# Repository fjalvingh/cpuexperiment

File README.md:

# Experiments with a am29xx based CPU

The am29xx series of bitslice CPU parts were a big thing when they arrived, and they have been used in many vintage designs. I find them interesting because they are still reasonably simple to understand, and they do replace a large amount of TTL logic for a homebrew CPU. I got a few of these parts from different places and decided to play with them to get an idea on how they work.

To do that the plan is to build some parts for a real CPU. It is not intended to be finished, it is intended to teach me and help me understand these parts, and to help me understand what is important in a CPU design using them.

## Process

NONE OF THIS IS READY FOR ANYTHING!! DO NOT ORDER BOARDS, they will not work ;)

### The ALU, getting to know the am2901

I am starting with the ALU part as I got 4 am2901's in my parts bin ;) I want to make a 16 bit ALU out of them, and the 2901's would also contain the generic register set (r0..r15).
I did consider breadboarding that, but 16 bits is a lot of wires, reliable breadboards are pretty expensive, and I really, *really* did not feel like wiring that all up...
So instead I created a Kicad schematic hoping that I would not be too far off, and I created a PCB using the Autorouter to route most traces so that I would not waste time on that. It is a 2 layer board so making fixes for the mistakes I've undoubtedly made should not be too difficult.

The board has 4x am2901, some glue logic to detect condition codes, a lot of leds to show ALU function inputs, and two sockets for my [8 bit bus to hex display](https://github.com/fjalvingh/8bit-busdisplay) so that we can easily follow what is happening.

The board uses two 40 pin double row pin headers (female) as a connector to a later possible backplane, as these are cheap and relatively reliable. And they make it easy to exercise the board using an Arduino Mega 2560.

A picture of the completed board:

The wires into the connectors are breadboard patch wires, and they prove to be useless, so the next try is to make real pin header wires to the Arduino.

### Playing with the board

After creating proper cabling between the Arduino and the ALU board:

at least everything worked consistently. But writing Arduino programs makes it a bit hard to do a lot of testing. So the next part is to make the Arduino a slave board that gets commands over USB Serial from a Java program. The Java program sends simple packets consisting of a command code, parameter values and a checksum. The Arduino waits for commands on its bus, decodes the packets, then executes the command. After that it sends either an error packet or a response packet back with any results for the command.

These are the programs under aluboard-controller and aluboard-arduino.

## Progress

* 2025/11/28 Added basic Java GUI and an Arduino program to test the ALU board
* 2025/11/23 Created this Github repo
* 2025/10/18 Started the ALU Kicad design

## Documentation used

I am using the following documents to make sense of everything.

### AM29xx series:
 
* [The AM2900 family data book](documentation/1978_The_Am2900_Family_Data_Book.pdf)
* [The am2901 datasheet](documentation/AM2901-AdvancedMicroDevices.pdf)
* [The am2910 datasheet](documentation/am2910.pdf)
* [Bit Slice microprocessor design](http://www.bitsavers.org/components/amd/bitslice/Mick_Bit-Slice_Microprocessor_Design_1980.pdf) by John Mick and Jim Brick
* [am2910 application note: programming the 2910](documentation/Am2910_apnote_Programming%20the.pdf)
* A more readable [am2901 block diagram](documentation/am2901-blockdiagram.jpg)
* Bit slice design - controllers and ALUs by [Donnamaie White](https://www.donnamaie.com/) - whose site has a lot of other interesting information.
* The "Build a microcomputer" series of appnotes, also [on the site of Donnamaie White, here](https://www.donnamaie.com/AMD_2900.html).
* [A microprogrammed computer](documentation/16-bit%20computer%20book.pdf), also from Donnamaie's site.

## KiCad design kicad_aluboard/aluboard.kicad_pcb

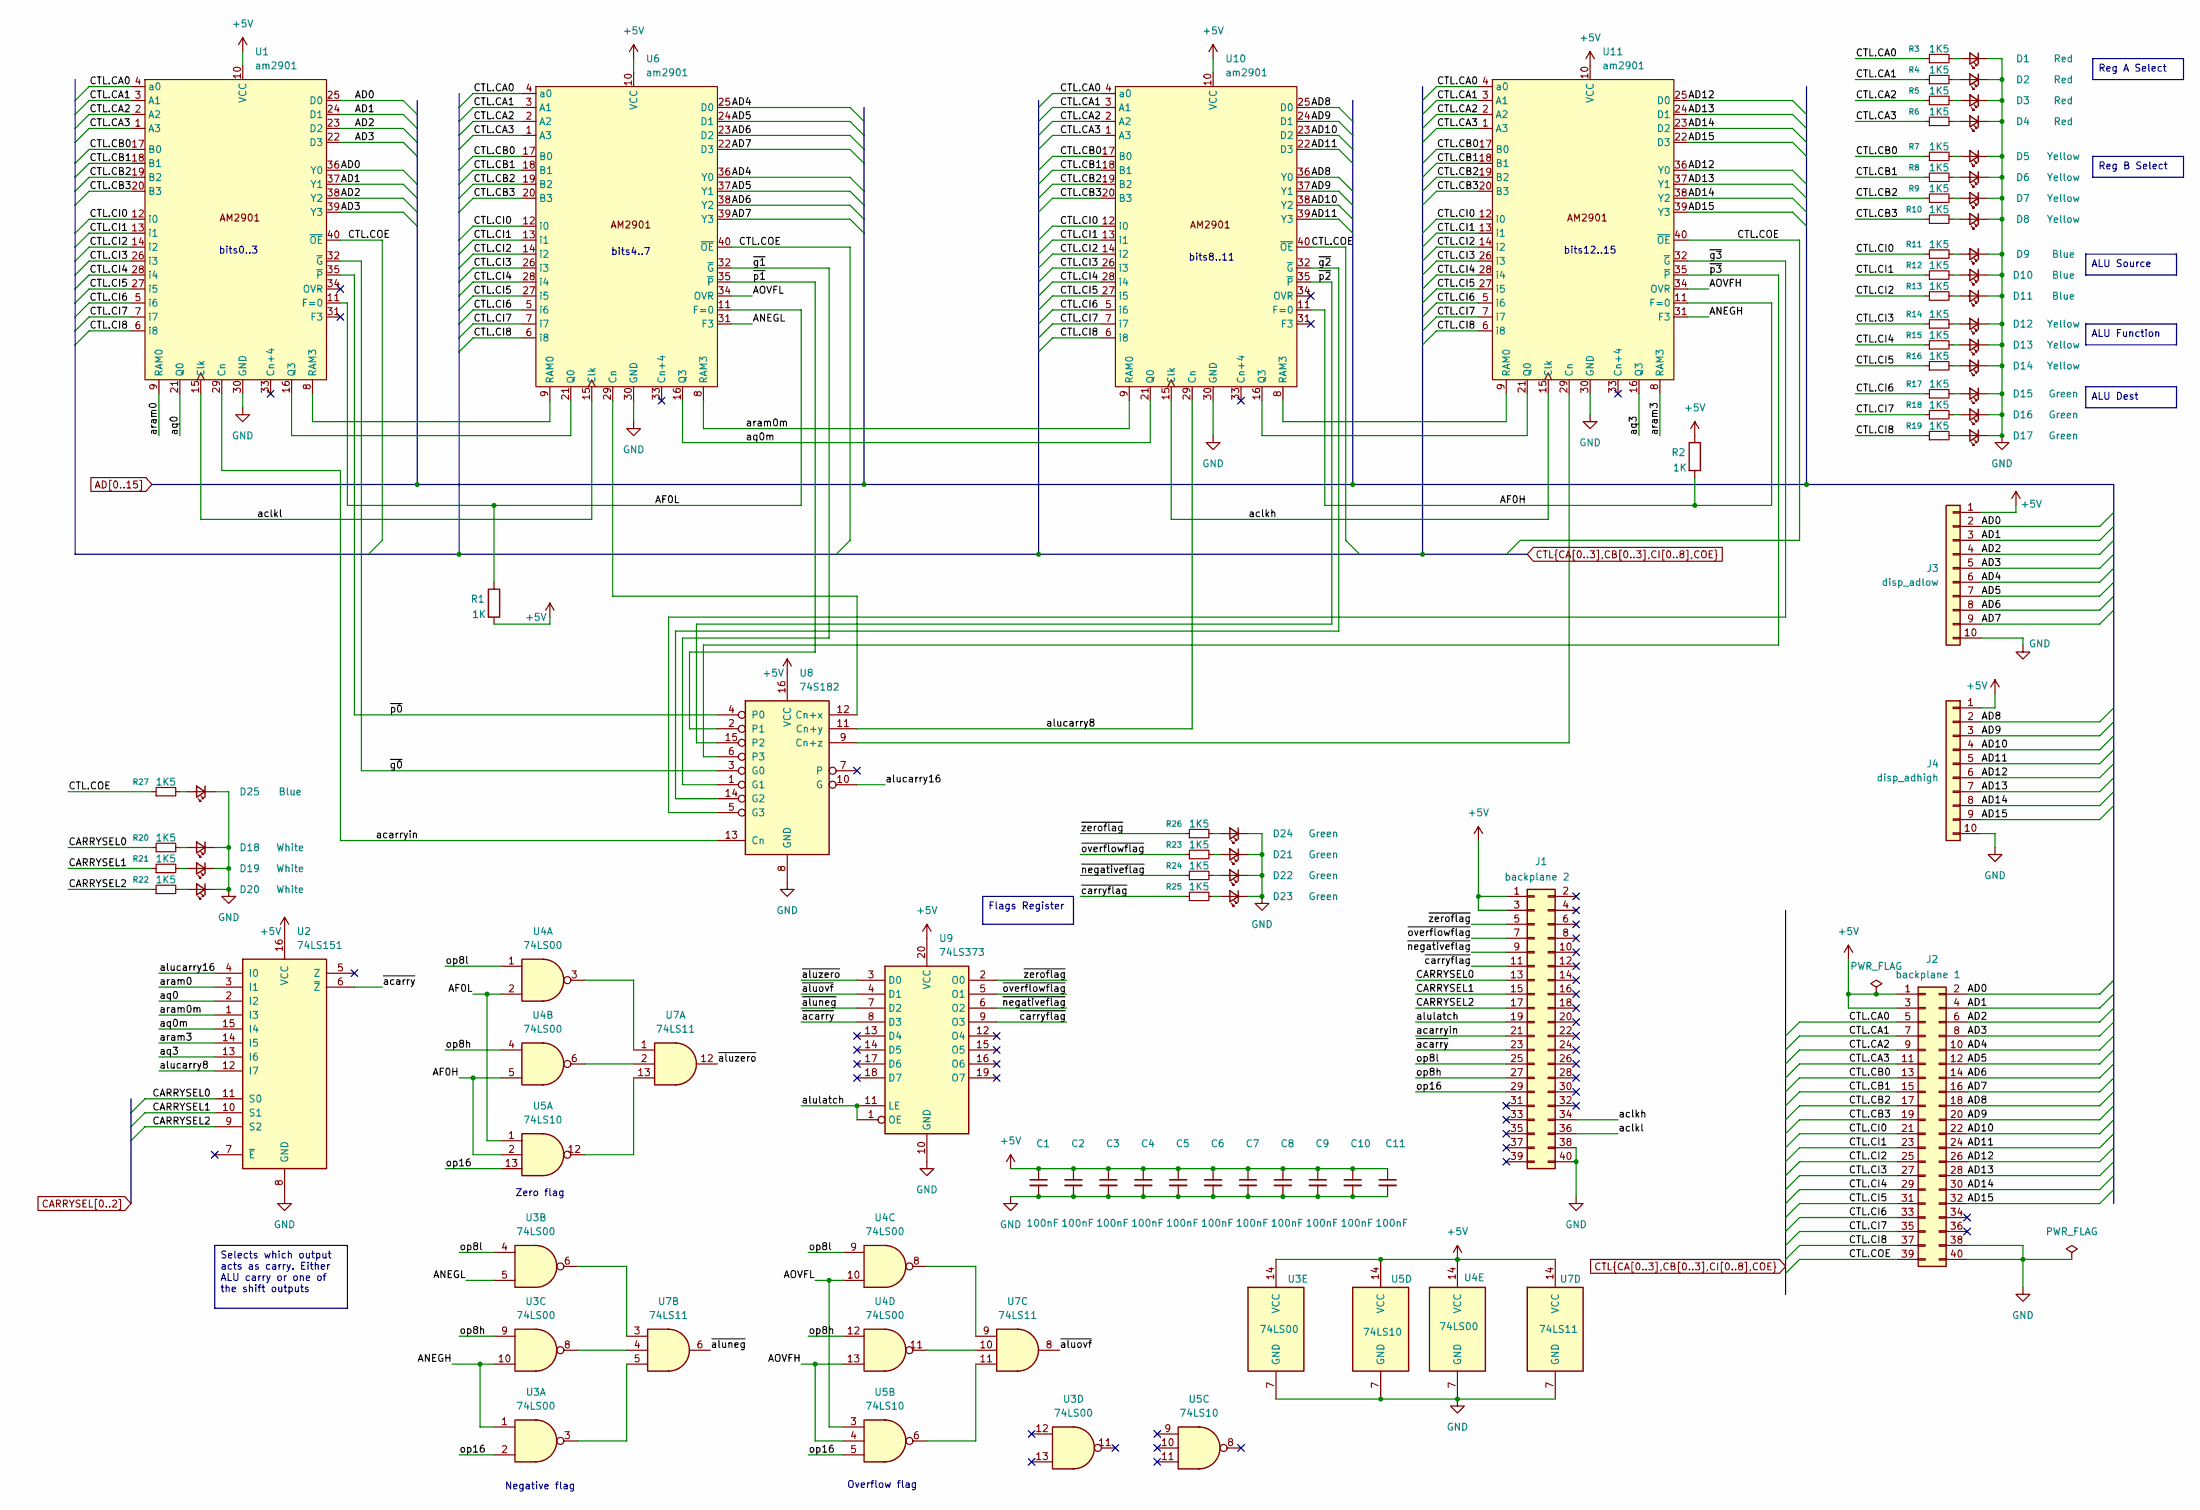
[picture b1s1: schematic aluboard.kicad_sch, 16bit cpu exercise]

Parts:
C1, C2, C3, C4, C5, C6, C7, C8, C9, C10, C11: 100nF; C_Disc_D3.8mm_W2.6mm_P2.50mm
D1, D2, D3, D4: Red; LED_0805_2012Metric_Pad1.15x1.40mm_HandSolder
D5, D6, D7, D8, D12, D13, D14: Yellow; LED_0805_2012Metric_Pad1.15x1.40mm_HandSolder
D9, D10, D11, D25: Blue; LED_0805_2012Metric_Pad1.15x1.40mm_HandSolder
D15, D16, D17, D21, D22, D23, D24: Green; LED_0805_2012Metric_Pad1.15x1.40mm_HandSolder
D18, D19, D20: White; LED_0805_2012Metric_Pad1.15x1.40mm_HandSolder
J1: backplane 2; PinSocket_2x20_P2.54mm_Horizontal
J2: backplane 1; PinSocket_2x20_P2.54mm_Horizontal
J3: disp_adlow; PinSocket_1x10_P2.54mm_Vertical
J4: disp_adhigh; PinSocket_1x10_P2.54mm_Vertical
R1, R2: 1K; R_Axial_DIN0207_L6.3mm_D2.5mm_P7.62mm_Horizontal
R3, R4, R5, R6, R7, R8, R9, R10, R11, R12, R13, R14, R15, R16, R17, R18, R19, R20, R21, R22, R23, R24, R25, R26, R27: 1K5; R_0805_2012Metric
U1, U6, U10, U11: am2901; DIP-40_W15.24mm_Socket_LongPads
U2: 74LS151; DIP-16_W7.62mm_Socket_LongPads
U3, U4: 74LS00; DIP-14_W7.62mm_Socket_LongPads
U5: 74LS10; DIP-14_W7.62mm_Socket_LongPads
U7: 74LS11; DIP-14_W7.62mm_Socket_LongPads
U8: 74S182; DIP-16_W7.62mm_Socket_LongPads
U9: 74LS373; DIP-20_W7.62mm_Socket_LongPads

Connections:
+5V: C1.1, C2.1, C3.1, C4.1, C5.1, C6.1, C7.1, C8.1, C9.1, C10.1, C11.1, J1.1, J1.3, J2.1, J2.3, J3.1, J4.1, R1.2, R2.1, U1.10 (VCC), U2.16 (VCC), U3.14 (VCC), U4.14 (VCC), U5.14 (VCC), U6.10 (VCC), U7.14 (VCC), U8.16 (VCC), U9.20 (VCC), U10.10 (VCC), U11.10 (VCC)
/AF0H: R2.2, U4.5, U5.2, U10.11 (F=0), U11.11 (F=0)
/AF0L: R1.1, U1.11 (F=0), U4.2, U5.1, U6.11 (F=0)
/ANEGH: U3.1, U3.10, U11.31 (F3)
/ANEGL: U3.5, U6.31 (F3)
/AOVFH: U4.13, U5.4, U11.34 (OVR)
/AOVFL: U4.10, U5.3, U6.34 (OVR)
/acarryin: J1.21, U1.29 (Cn), U8.13 (Cn)
/aclkh: J1.34, U10.15 (Clk), U11.15 (Clk)
/aclkl: J1.36, U1.15 (Clk), U6.15 (Clk)
/alucarry8: U2.12 (I7), U8.11 (Cn+y), U10.29 (Cn)
/alucarry16: U2.4 (I0), U8.10 (G)
/alulatch: J1.19, U9.1 (OE), U9.11 (LE)
/aq0: U1.21 (Q0), U2.2 (I2)
/aq0m: U2.15 (I4), U6.16 (Q3), U10.21 (Q0)
/aq3: U2.13 (I6), U11.16 (Q3)
/aram0: U1.9 (RAM0), U2.3 (I1)
/aram0m: U2.1 (I3), U6.8 (RAM3), U10.9 (RAM0)
/aram3: U2.14 (I5), U11.8 (RAM3)
/op8h: J1.27, U3.9, U4.4, U4.12
/op8l: J1.25, U3.4, U4.1, U4.9
/op16: J1.29, U3.2, U5.5, U5.13
/~acarry: J1.23, U2.6 (~Z), U9.8 (D3)
/~aluneg: U7.6, U9.7 (D2)
/~aluovf: U7.8, U9.4 (D1)
/~aluzero: U7.12, U9.3 (D0)
/~carryflag: J1.11, R25.1, U9.9 (O3)
/~g0: U1.32 (~G), U8.3 (G0)
/~g1: U6.32 (~G), U8.1 (G1)
/~g2: U8.14 (G2), U10.32 (~G)
/~g3: U8.5 (G3), U11.32 (~G)
/~negativeflag: J1.9, R24.1, U9.6 (O2)
/~overflowflag: J1.7, R23.1, U9.5 (O1)
/~p0: U1.35 (~P), U8.4 (P0)
/~p1: U6.35 (~P), U8.2 (P1)
/~p2: U8.15 (P2), U10.35 (~P)
/~p3: U8.6 (P3), U11.35 (~P)
/~zeroflag: J1.5, R26.1, U9.2 (O0)
AD0: J2.2, J3.2, U1.25 (D0), U1.36 (Y0)
AD1: J2.4, J3.3, U1.24 (D1), U1.37 (Y1)
AD2: J2.6, J3.4, U1.23 (D2), U1.38 (Y2)
AD3: J2.8, J3.5, U1.22 (D3), U1.39 (Y3)
AD4: J2.10, J3.6, U6.25 (D0), U6.36 (Y0)
AD5: J2.12, J3.7, U6.24 (D1), U6.37 (Y1)
AD6: J2.14, J3.8, U6.23 (D2), U6.38 (Y2)
AD7: J2.16, J3.9, U6.22 (D3), U6.39 (Y3)
AD8: J2.18, J4.2, U10.25 (D0), U10.36 (Y0)
AD9: J2.20, J4.3, U10.24 (D1), U10.37 (Y1)
AD10: J2.22, J4.4, U10.23 (D2), U10.38 (Y2)
AD11: J2.24, J4.5, U10.22 (D3), U10.39 (Y3)
AD12: J2.26, J4.6, U11.25 (D0), U11.36 (Y0)
AD13: J2.28, J4.7, U11.24 (D1), U11.37 (Y1)
AD14: J2.30, J4.8, U11.23 (D2), U11.38 (Y2)
AD15: J2.32, J4.9, U11.22 (D3), U11.39 (Y3)
CARRYSEL0: J1.13, R20.1, U2.11 (S0)
CARRYSEL1: J1.15, R21.1, U2.10 (S1)
CARRYSEL2: J1.17, R22.1, U2.9 (S2)
CTL.CA0: J2.5, R3.1, U1.4 (a0), U6.4 (a0), U10.4 (a0), U11.4 (a0)
CTL.CA1: J2.7, R4.1, U1.3 (A1), U6.3 (A1), U10.3 (A1), U11.3 (A1)
CTL.CA2: J2.9, R5.1, U1.2 (A2), U6.2 (A2), U10.2 (A2), U11.2 (A2)
CTL.CA3: J2.11, R6.1, U1.1 (A3), U6.1 (A3), U10.1 (A3), U11.1 (A3)
CTL.CB0: J2.13, R7.1, U1.17 (B0), U6.17 (B0), U10.17 (B0), U11.17 (B0)
CTL.CB1: J2.15, R8.1, U1.18 (B1), U6.18 (B1), U10.18 (B1), U11.18 (B1)
CTL.CB2: J2.17, R9.1, U1.19 (B2), U6.19 (B2), U10.19 (B2), U11.19 (B2)
CTL.CB3: J2.19, R10.1, U1.20 (B3), U6.20 (B3), U10.20 (B3), U11.20 (B3)
CTL.CI0: J2.21, R11.1, U1.12 (i0), U6.12 (i0), U10.12 (i0), U11.12 (i0)
CTL.CI1: J2.23, R12.1, U1.13 (i1), U6.13 (i1), U10.13 (i1), U11.13 (i1)
CTL.CI2: J2.25, R13.1, U1.14 (i2), U6.14 (i2), U10.14 (i2), U11.14 (i2)
CTL.CI3: J2.27, R14.1, U1.26 (i3), U6.26 (i3), U10.26 (i3), U11.26 (i3)
CTL.CI4: J2.29, R15.1, U1.28 (i4), U6.28 (i4), U10.28 (i4), U11.28 (i4)
CTL.CI5: J2.31, R16.1, U1.27 (i5), U6.27 (i5), U10.27 (i5), U11.27 (i5)
CTL.CI6: J2.33, R17.1, U1.5 (i6), U6.5 (i6), U10.5 (i6), U11.5 (i6)
CTL.CI7: J2.35, R18.1, U1.7 (i7), U6.7 (i7), U10.7 (i7), U11.7 (i7)
CTL.CI8: J2.37, R19.1, U1.6 (i8), U6.6 (i8), U10.6 (i8), U11.6 (i8)
CTL.COE: J2.39, R27.1, U1.40 (~OE), U6.40 (~OE), U10.40 (~OE), U11.40 (~OE)
GND: C1.2, C2.2, C3.2, C4.2, C5.2, C6.2, C7.2, C8.2, C9.2, C10.2, C11.2, D1.1 (K), D2.1 (K), D3.1 (K), D4.1 (K), D5.1 (K), D6.1 (K), D7.1 (K), D8.1 (K), D9.1 (K), D10.1 (K), D11.1 (K), D12.1 (K), D13.1 (K), D14.1 (K), D15.1 (K), D16.1 (K), D17.1 (K), D18.1 (K), D19.1 (K), D20.1 (K), D21.1 (K), D22.1 (K), D23.1 (K), D24.1 (K), D25.1 (K), J1.38, J1.40, J2.38, J2.40, J3.10, J4.10, U1.30 (GND), U2.8 (GND), U3.7 (GND), U4.7 (GND), U5.7 (GND), U6.30 (GND), U7.7 (GND), U8.8 (GND), U9.10 (GND), U10.30 (GND), U11.30 (GND)
unnamed: D1.2 (A), R3.2
unnamed: D2.2 (A), R4.2
unnamed: D3.2 (A), R5.2
unnamed: D4.2 (A), R6.2
unnamed: D5.2 (A), R7.2
unnamed: D6.2 (A), R8.2
unnamed: D7.2 (A), R9.2
unnamed: D8.2 (A), R10.2
unnamed: D9.2 (A), R11.2
unnamed: D10.2 (A), R12.2
unnamed: D11.2 (A), R13.2
unnamed: D12.2 (A), R14.2
unnamed: D13.2 (A), R15.2
unnamed: D14.2 (A), R16.2
unnamed: D15.2 (A), R17.2
unnamed: D16.2 (A), R18.2
unnamed: D17.2 (A), R19.2
unnamed: D18.2 (A), R20.2
unnamed: D19.2 (A), R21.2
unnamed: D20.2 (A), R22.2
unnamed: D21.2 (A), R23.2
unnamed: D22.2 (A), R24.2
unnamed: D23.2 (A), R25.2
unnamed: D24.2 (A), R26.2
unnamed: D25.2 (A), R27.2
unnamed: U1.16 (Q3), U6.21 (Q0)
unnamed: U1.8 (RAM3), U6.9 (RAM0)
unnamed: U3.3, U7.5
unnamed: U3.6, U7.3
unnamed: U3.8, U7.4
unnamed: U4.3, U7.1
unnamed: U4.6, U7.2
unnamed: U4.8, U7.9
unnamed: U4.11, U7.10
unnamed: U5.6, U7.11
unnamed: U5.12, U7.13
unnamed: U6.29 (Cn), U8.12 (Cn+x)
unnamed: U10.16 (Q3), U11.21 (Q0)
unnamed: U10.8 (RAM3), U11.9 (RAM0)
unnamed: U8.9 (Cn+z), U11.29 (Cn)

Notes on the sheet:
Overflow flag
bits8..11
bits0..3
Zero flag
bits4..7
bits12..15
Negative flag
Selects which output acts as carry. Either ALU carry or one of the shift outputs
Reg B Select
Reg A Select
Flags Register
ALU Function
ALU Dest
ALU Source

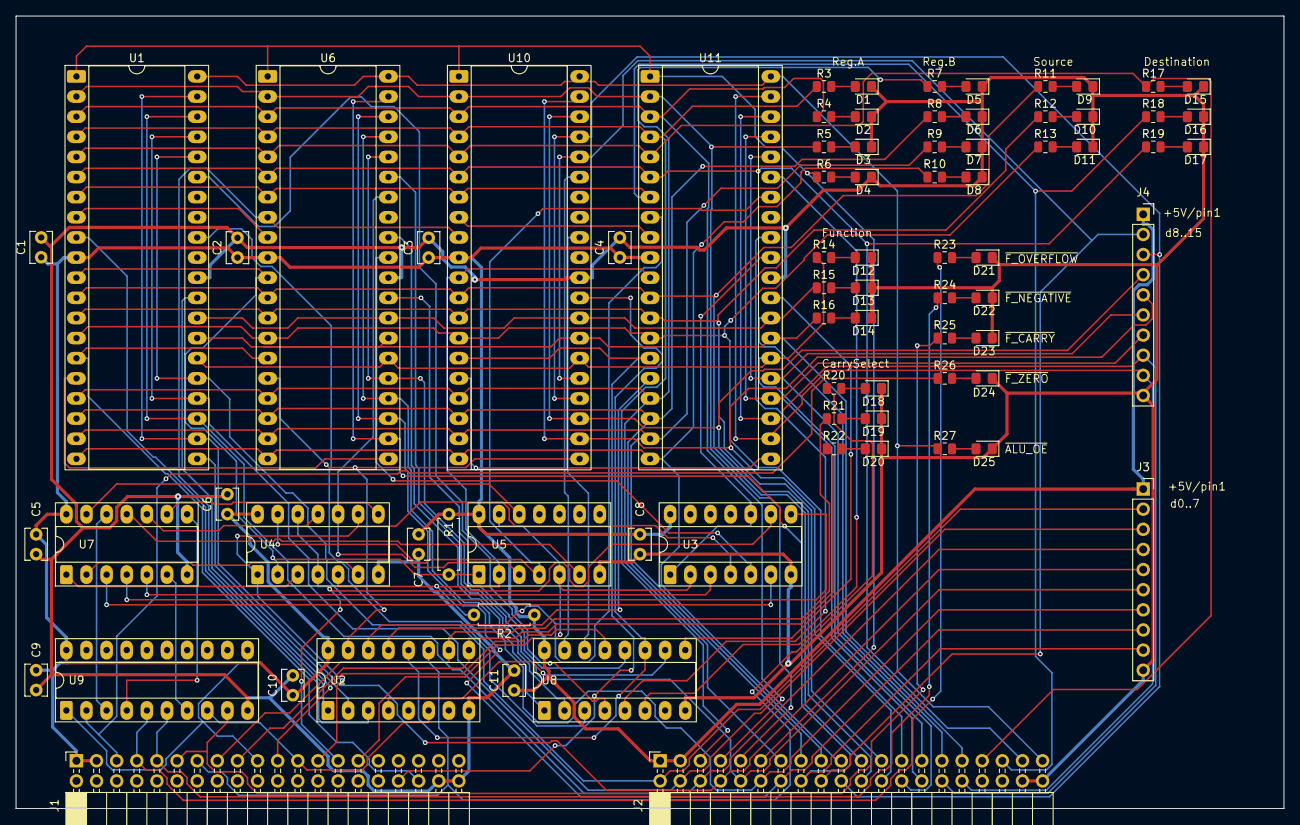
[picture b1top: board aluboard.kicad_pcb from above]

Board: 2 copper layers, 160.0 x 100.0 mm, 79 parts (1 on the bottom side), 116 nets.

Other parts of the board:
logo: LOGO

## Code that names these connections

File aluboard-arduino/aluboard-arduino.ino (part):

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#define CTL_OP8H    (ARDUINO_A0 + 5)
#define CTL_OP8L    (ARDUINO_A0 + 6)

#define ACARRYIN    (ARDUINO_A0 + 7)      // ALU Carry in
#define FLAGSLATCH  (ARDUINO_A0 + 8)      // Flags register latch

#define CARRYSEL2   (ARDUINO_A0 + 9)      // Carry flag source. Watch out: reversed!
#define CARRYSEL1   (ARDUINO_A0 + 10)
#define CARRYSEL0   (ARDUINO_A0 + 11)

#define FLGCARRYL   (ARDUINO_A0 + 12)     // Carry flag, L active
#define FLGNEGL     (ARDUINO_A0 + 13)
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  digitalWrite(CTL_CLKAL, LOW);             // Latched A and B
  digitalWrite(CTL_CLKAH, LOW);

  pinMode(ACARRYIN, OUTPUT);
  digitalWrite(ACARRYIN, LOW);              // Carry in 0

  pinMode(FLAGSLATCH, OUTPUT);
  // digitalWrite(FLAGSLATCH, HIGH);           // Let flag values roll through (not latched)
  digitalWrite(FLAGSLATCH, LOW);

  pinMode(CARRYSEL0, OUTPUT);
  pinMode(CARRYSEL1, OUTPUT);
  pinMode(CARRYSEL2, OUTPUT);
  digitalWrite(CARRYSEL0, LOW);
  digitalWrite(CARRYSEL1, LOW);
  digitalWrite(CARRYSEL2, LOW);
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
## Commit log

2025-11-23 Initial commit.
2025-11-23 Redoing control board because of pipeline blunder. This also is the last version with the distinct program counter.
2025-11-24 [control] work in progress
2025-11-28 [alucontroller] Add initial version of ALU board controller, showing register contents only
2025-11-28 [aluboard] Add Arduino tester application for alucontroller
2025-11-28 [aluboard] Arduino IDE wants a different name.
2025-11-29 [aluboard] Fixes, added read/update registers functions and buttons
2025-11-30 [aluboard] Add alu operation UI
2025-11-30 [aluboard] first-run fixes for alu operation ui
2025-12-02 [aluboard] Remove delays, add commands to zero and init regs, add carry selector and flag UI
2025-12-14 [aluboard] Fix remarks
2025-12-14 [alu] Add code to read Q and flags.
2025-12-21 [alu] Show flag values.
2025-12-26 [alu] Latch flahs with clock=low to get REAL flag status

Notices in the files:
kicad_aluboard/aluboard.kicad_pcb:
(c)2025 ErrorSoft
